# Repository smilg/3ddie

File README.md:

# 3ddie
3D Digital Interface, EPIC!

## Project Structure
[3ddie/](3ddie/): contains the Kicad (6.x) project for 3ddie. This includes the schematic, board layout, [BOM](3ddie/3ddie-bom-cleaned.csv), symbols, and footprints.

[mcad/](mcad/): contains SOLIDWORKS assembly files for 3ddie and the beginnings of a case.

[firmware/](firmware/): contains firmware for 3ddie. Currently, this only includes the start of the I²C to USB bridge firmware for the RP2040 to allow connection between the MGC3130 and Microchip's Aurea software. The submodules in that folder are projects that we are basing this off of.

[silkscreen_images/](silkscreen_images/): contains the image files for the silkscreen art on the PCB. These were converted to footprints using Kicad's built-in tool.

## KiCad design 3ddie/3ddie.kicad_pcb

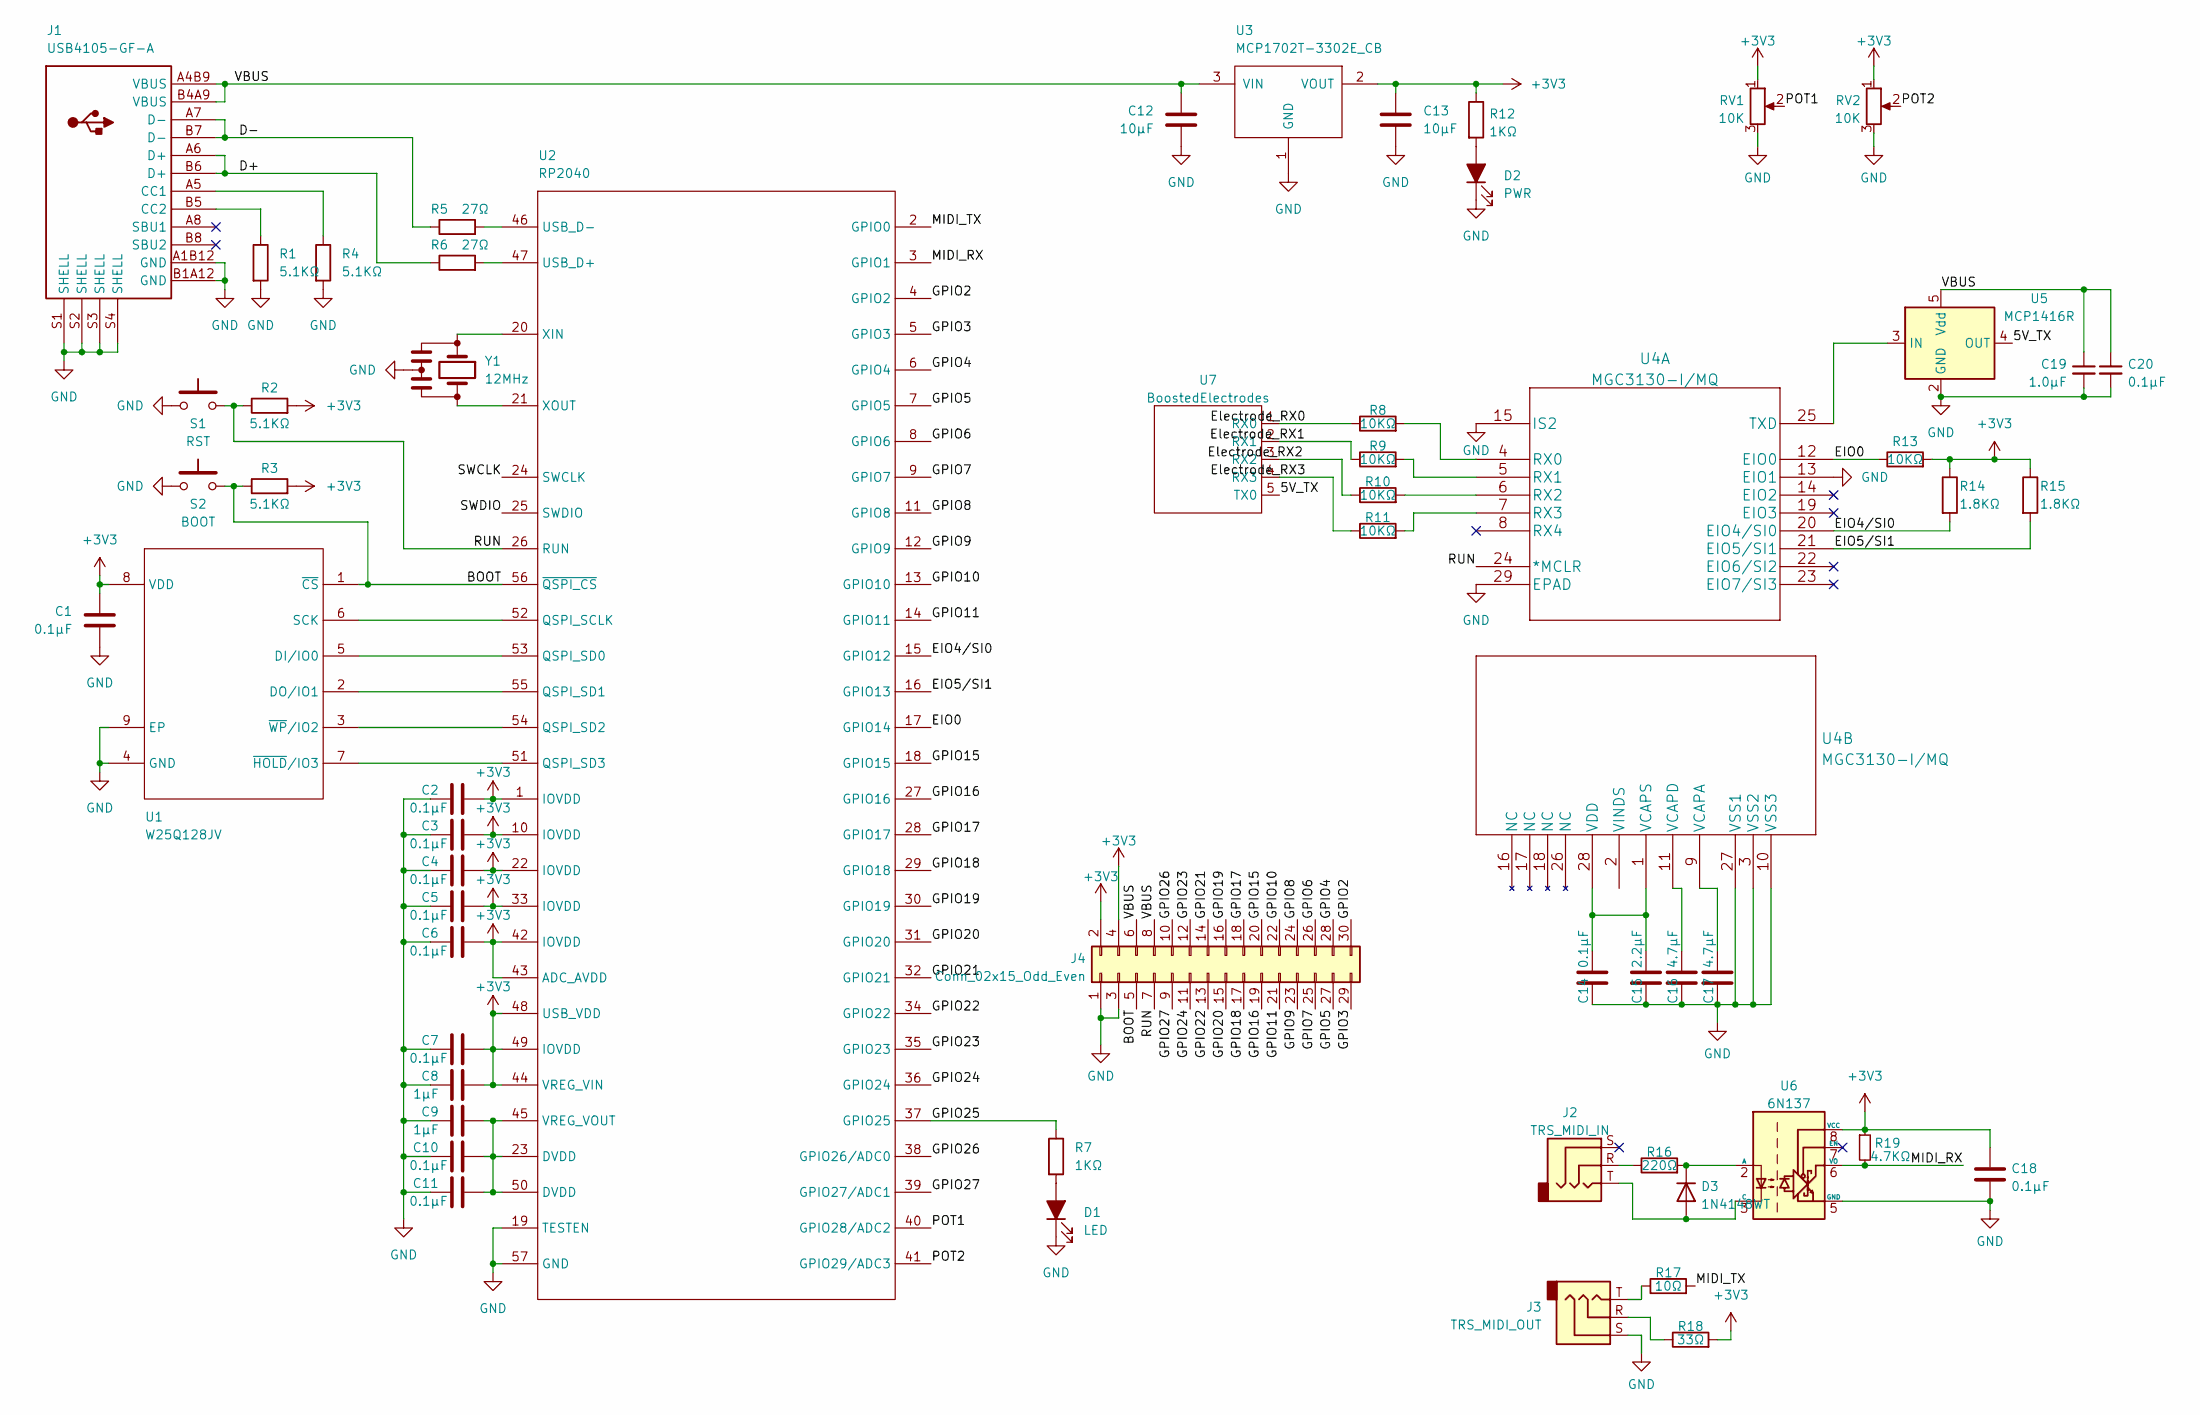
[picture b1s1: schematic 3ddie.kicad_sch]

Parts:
C1: 0.1µF; C_0603_1608Metric
C2, C3, C4, C5, C6, C7, C10, C11: 0.1µF; C_0402_1005Metric
C8, C9: 1µF; C_0402_1005Metric
C12, C13: 10µF; C_0603_1608Metric
C14, C18, C20: 0.1μF; C_0603_1608Metric
C15: 2.2μF; C_0603_1608Metric
C16, C17: 4.7μF; C_0603_1608Metric
C19: 1.0μF; C_0603_1608Metric
D1: LED; LED_0805_2012Metric; Digikey Catalog # 160-1887-1-ND
D2: PWR; LED_0805_2012Metric; Digikey Catalog # 160-1427-1-ND
D3: 1N4148WT; D_SOD-523; Manufacturer Part # 1N4148WT; Digikey Catalog # 1N4148WTCT-ND
J1: USB4105-GF-A; Manufacturer Part # USB4105-GF-A; Digikey Catalog # 2073-USB4105-GF-ACT-ND
J2: TRS_MIDI_IN; Jack_3.5mm_CUI_SJ1-3533NG_Horizontal; Manufacturer Part # SJ1-3533NG; Digikey Catalog # CP1-3533NG-ND
J3: TRS_MIDI_OUT; Jack_3.5mm_CUI_SJ1-3533NG_Horizontal; Manufacturer Part # SJ1-3533NG; Digikey Catalog # CP1-3533NG-ND
J4: Conn_02x15_Odd_Even; IDC-Header_2x15_P2.54mm_Horizontal
R1, R2, R3, R4: 5.1KΩ; R_0603_1608Metric
R5, R6: 27Ω; R_0402_1005Metric
R7, R12: 1KΩ; R_0603_1608Metric
R8, R9, R10, R11, R13: 10KΩ; R_0603_1608Metric
R14, R15: 1.8KΩ; R_0603_1608Metric
R16: 220Ω; R_0603_1608Metric
R17: 10Ω; R_0603_1608Metric
R18: 33Ω; R_0603_1608Metric
R19: 4.7KΩ; R_0603_1608Metric
RV1, RV2: 10K; PDB12-H4251-103BF
S1: RST; TL3301AFxxxxJ; Manufacturer Part # KTX 321 LHS; Digikey Catalog # CKN10778CT-ND
S2: BOOT; TL3301AFxxxxJ; Manufacturer Part # KTX 321 LHS; Digikey Catalog # CKN10778CT-ND
U1: W25Q128JV; MIC_WSON-8; Manufacturer Part # W25Q128JVPIM TR; Digikey Catalog # W25Q128JVPIMCT-ND
U2: RP2040; Manufacturer Part # SC0914(13); Digikey Catalog # 2648-SC0914(13)CT-ND
U3: MCP1702T-3302E_CB; SOT-23; Manufacturer Part # MCP1702T-3302E/CB; Digikey Catalog # MCP1702T-3302E/CBCT-ND
U4: MGC3130-I/MQ; MGC3130T-I_MQ; Manufacturer Part # MGC3130-I/MQ; Digikey Catalog # MGC3130-I/MQ-ND
U5: MCP1416R; SOT-23-5; Manufacturer Part # MCP1416RT-E/OT; Digikey Catalog # MCP1416RT-E/OTCT-ND
U6: 6N137; 6N137_Leadbend; Manufacturer Part # 6N137SM; Digikey Catalog # 6N137SM-ND
U7: BoostedElectrodes
Y1: 12MHz; CSTNE; Manufacturer Part # CSTNE12M0G55A000R0; Digikey Catalog # 490-17944-1-ND

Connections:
+3V3: C1.2, C2.1, C3.1, C4.1, C5.1, C6.1, C7.1, C8.1, C13.1, C18.1, J4.2, J4.4, R2.2, R3.2, R12.1, R13.2, R14.1, R15.1, R18.2, R19.1, RV1.1, RV2.1, U1.8 (VDD), U2.1 (IOVDD), U2.10 (IOVDD), U2.22 (IOVDD), U2.33 (IOVDD), U2.42 (IOVDD), U2.43 (ADC_AVDD), U2.44 (VREG_VIN), U2.48 (USB_VDD), U2.49 (IOVDD), U3.2 (VOUT), U6.8 (VCC)
/5V_TX: U5.4 (OUT), U7.5 (TX0)
/BOOT: J4.5, R3.1, S2.2, U1.1 (~CS), U2.56 (~QSPI_CS)
/D+: J1.A6 (D+), J1.B6 (D+), R6.1
/D-: J1.A7 (D-), J1.B7 (D-), R5.1
/EIO0: R13.1, U2.17 (GPIO14), U4.12 (EIO0)
/EIO4/SI0: R14.2, U2.15 (GPIO12), U4.20 (EIO4/SI0)
/EIO5/SI1: R15.2, U2.16 (GPIO13), U4.21 (EIO5/SI1)
/Electrode_RX0: R8.1, U7.1 (RX0)
/Electrode_RX1: R9.1, U7.2 (RX1)
/Electrode_RX2: R10.1, U7.3 (RX2)
/Electrode_RX3: R11.1, U7.4 (RX3)
/GPIO2: J4.30, U2.4 (GPIO2)
/GPIO3: J4.29, U2.5 (GPIO3)
/GPIO4: J4.28, U2.6 (GPIO4)
/GPIO5: J4.27, U2.7 (GPIO5)
/GPIO6: J4.26, U2.8 (GPIO6)
/GPIO7: J4.25, U2.9 (GPIO7)
/GPIO8: J4.24, U2.11 (GPIO8)
/GPIO9: J4.23, U2.12 (GPIO9)
/GPIO10: J4.22, U2.13 (GPIO10)
/GPIO11: J4.21, U2.14 (GPIO11)
/GPIO15: J4.20, U2.18 (GPIO15)
/GPIO16: J4.19, U2.27 (GPIO16)
/GPIO17: J4.18, U2.28 (GPIO17)
/GPIO18: J4.17, U2.29 (GPIO18)
/GPIO19: J4.16, U2.30 (GPIO19)
/GPIO20: J4.15, U2.31 (GPIO20)
/GPIO21: J4.14, U2.32 (GPIO21)
/GPIO22: J4.13, U2.34 (GPIO22)
/GPIO23: J4.12, U2.35 (GPIO23)
/GPIO24: J4.11, U2.36 (GPIO24)
/GPIO25: R7.1, U2.37 (GPIO25)
/GPIO26: J4.10, U2.38 (GPIO26/ADC0)
/GPIO27: J4.9, U2.39 (GPIO27/ADC1)
/MIDI_RX: R19.2, U2.3 (GPIO1), U6.6 (VO)
/MIDI_TX: R17.2, U2.2 (GPIO0)
/POT1: RV1.2, U2.40 (GPIO28/ADC2)
/POT2: RV2.2, U2.41 (GPIO29/ADC3)
/RUN: J4.7, R2.1, S1.2, U2.26 (RUN), U4.24 (*MCLR)
/SWCLK: U2.24 (SWCLK)
/SWDIO: U2.25 (SWDIO)
/VBUS: C12.2, C19.1, C20.1, J1.A4B9 (VBUS), J1.B4A9 (VBUS), J4.6, J4.8, U3.3 (VIN), U5.5 (Vdd)
GND: C1.1, C2.2, C3.2, C4.2, C5.2, C6.2, C7.2, C8.2, C9.2, C10.2, C11.2, C12.1, C13.2, C14.1, C15.1, C16.1, C17.1, C18.2, C19.2, C20.2, D1.1 (K), D2.1 (K), J1.A1B12 (GND), J1.B1A12 (GND), J1.S1 (SHELL), J1.S2 (SHELL), J1.S3 (SHELL), J1.S4 (SHELL), J3.S, J4.1, J4.3, R1.2, R4.2, RV1.3, RV2.3, S1.1, S2.1, U1.4 (GND), U1.9 (EP), U2.19 (TESTEN), U2.57 (GND), U3.1 (GND), U4.3 (VSS2), U4.10 (VSS3), U4.13 (EIO1), U4.15 (IS2), U4.27 (VSS1), U4.29 (EPAD), U5.2 (GND), U6.5 (GND), Y1.2
unnamed: C9.1, C10.1, C11.1, U2.23 (DVDD), U2.45 (VREG_VOUT), U2.50 (DVDD)
unnamed: C14.2, C15.2, U4.1 (VCAPS), U4.28 (VDD)
unnamed: C16.2, U4.11 (VCAPD)
unnamed: C17.2, U4.9 (VCAPA)
unnamed: D1.2 (A), R7.2
unnamed: D2.2 (A), R12.2
unnamed: D3.1 (K), R16.2, U6.2 (A)
unnamed: D3.2 (A), J2.T, U6.3 (C)
unnamed: J1.A5 (CC1), R4.1
unnamed: J1.B5 (CC2), R1.1
unnamed: J2.R, R16.1
unnamed: J3.R, R18.1
unnamed: J3.T, R17.1
unnamed: R5.2, U2.46 (USB_D-)
unnamed: R6.2, U2.47 (USB_D+)
unnamed: R8.2, U4.4 (RX0)
unnamed: R9.2, U4.5 (RX1)
unnamed: R10.2, U4.6 (RX2)
unnamed: R11.2, U4.7 (RX3)
unnamed: U1.2 (DO/IO1), U2.55 (QSPI_SD1)
unnamed: U1.3 (~WP/IO2), U2.54 (QSPI_SD2)
unnamed: U1.5 (DI/IO0), U2.53 (QSPI_SD0)
unnamed: U1.6 (SCK), U2.52 (QSPI_SCLK)
unnamed: U1.7 (~HOLD/IO3), U2.51 (QSPI_SD3)
unnamed: U2.20 (XIN), Y1.1
unnamed: U2.21 (XOUT), Y1.3
unnamed: U4.25 (TXD), U5.3 (IN)

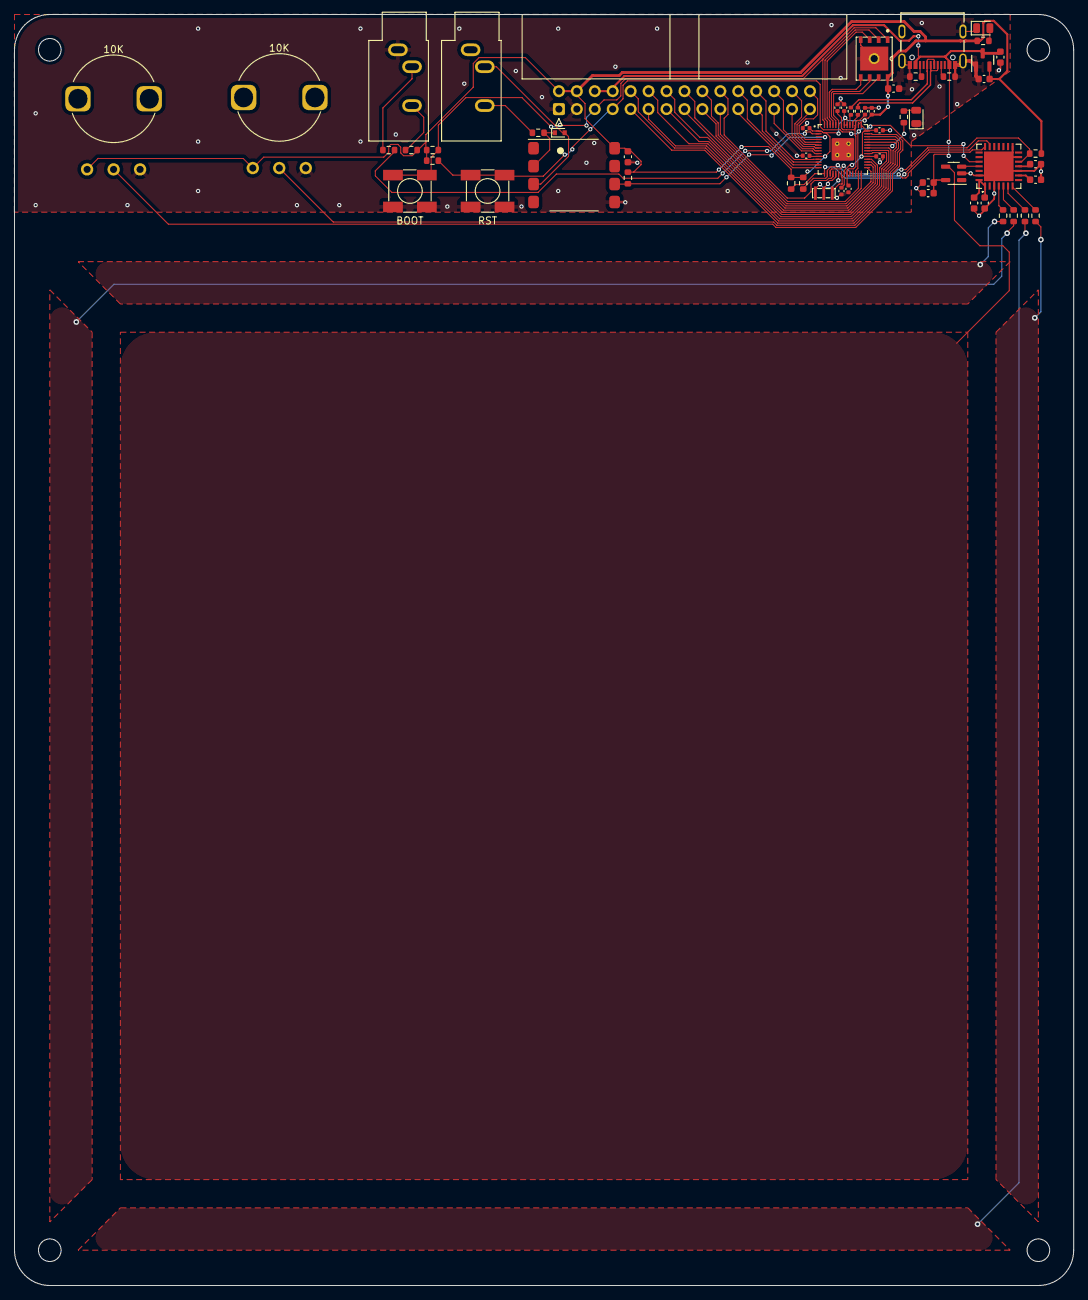
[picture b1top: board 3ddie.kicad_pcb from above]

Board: 2 copper layers, 150.0 x 180.0 mm, 57 parts (0 on the bottom side), 64 nets.

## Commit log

2022-10-23 meeting 10/23/22 initial schema
2022-10-23 add .gitignore for kicad and ds_store
2022-10-23 fix eclectronics library 3d model paths
2022-10-23 fix MGC3130 symbol and footprint, update schema
2022-10-25 In-class work 10/25
2022-10-31 add electrode schematic symbol
2022-10-31 connect electrodes, fill in title block, annotate symbols
2022-11-04 adding midi connectors and dac
2022-11-08 Remove DAC, rename pins from schem review
2022-11-08 annotate symbols, add value to optocoupler bypass cap
2022-11-08 update component value formatting for consistency
2022-11-08 fix symbol annotations
2022-11-08 add datasheet links, part numbers, and catalog numbers to symbols
2022-11-08 specify optocoupler diode, assign some footprints
2022-11-08 continue adding footprints
2022-11-08 create footprint for 6N137 according to datasheet
2022-11-08 finish assigning footprints (other than electrodes)
2022-11-12 add bypass caps to level shifter, start mgc portion of layout
2022-11-12 fill in pcb title block
2022-11-14 switch to through hole mounting trs jacks
2022-11-15 Adding pots, pin sockets, and footprints
2022-11-15 move eclectronics library into project directory
2022-11-15 get 3d model for 3.5mm jack
2022-11-15 continue layout
2022-11-16 expand board outline, add dimensions
2022-11-16 fix potentiometer footprint
2022-11-16 add 3d model to MGC3130 footprint
2022-11-16 continued routing
2022-11-17 layout and schema changes
2022-11-18 fix mgc footprint courtyard
2022-11-18 mostly finish routing and layout!
2022-11-18 rename symbol library to match project name, fix eclectronics lib path
2022-11-18 add silkscreen images
2022-11-18 clean up routing, add debug header, add silkscreen
2022-11-18 add date (nov 2022) to board
2022-11-18 fill in missing part numbers for bom prep
2022-11-18 exclude debug header from bom
2022-11-18 fix incorrect part numbers for buttons
2022-11-18 add bom
2022-11-18 increase thickness of face drawings
2022-12-01 replace incorrectly sized MGC3130 footprint with correct one, adjust schema and pcb accordingly
2022-12-01 swap 6n137 footprint for correct one, fix duplicate lines in mgc footprint, adjust layout
2022-12-01 fix MCLR line being connected to run, adjust routing
2022-12-01 fix mgc pin 1 indicator and 3d model
2022-12-01 update version number and date
2022-12-01 add 3d model to mgc footprint in library
2022-12-01 update version number and date in title blocks
2022-12-01 update solder paste layer for mgc
2022-12-01 tiny routing adjustment
2022-12-02 add 3d model for potentiometer
2022-12-02 setup firmware folder with sources to mash together
2022-12-03 set grid origin, change potentiometer 3d model from .iges to .step
2022-12-03 untrack .kicad_prl settings file
2022-12-03 change TRS jack 3d model from .igs to .step
2022-12-03 repair and add color to button 3d model
2022-12-03 fix usb c connector color
2022-12-06 add dual port cdc example from tinyusb
2022-12-06 move usb i2c bridge stuff into it's own subfolder
2022-12-06 add modified rp2040-i2c-interface as base for bridge
2022-12-06 modify tinyusb configuration to be CDC driver
2022-12-07 shrink mgc exposed pad paste, add drill origin
2022-12-07 add solidworks assembly for case design
2022-12-08 add notes on original sources, add .vscode dir to .gitignore
2022-12-21 fix readme typo
2023-11-20 add header footprint

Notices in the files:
parts and their libraries:
Copyright 2021 Accelerated Designs. All rights reserved.
